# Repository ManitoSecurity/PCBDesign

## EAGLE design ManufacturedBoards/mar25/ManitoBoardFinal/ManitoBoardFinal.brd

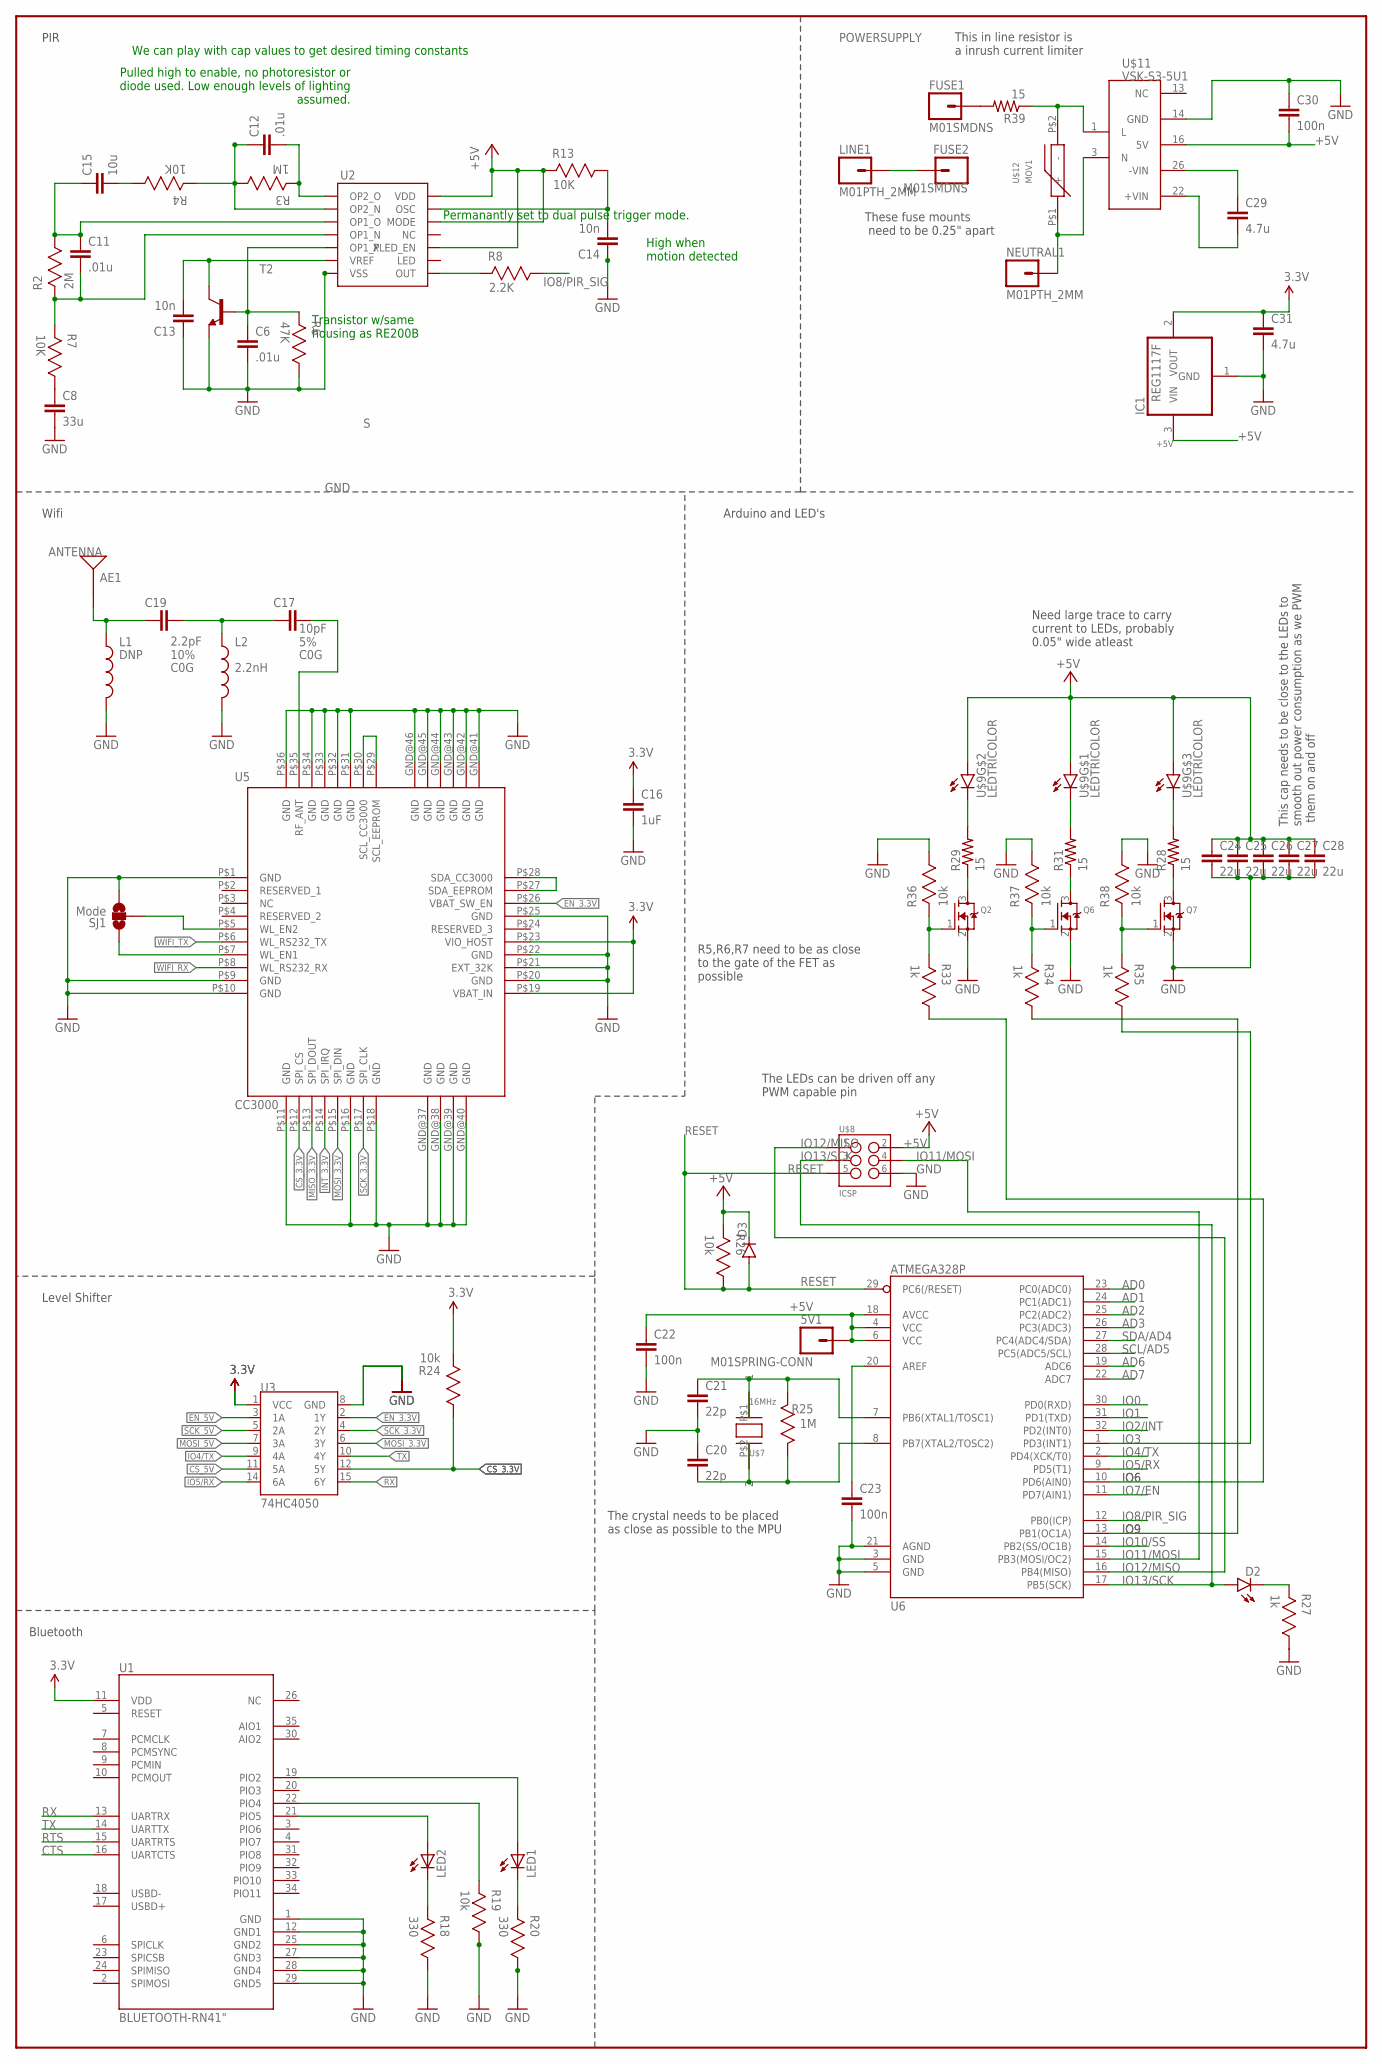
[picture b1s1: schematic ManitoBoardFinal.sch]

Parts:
5V1: M01SPRING-CONN; SPRING-CONNECTOR
AE1: ANTENNA; ANTENNA-CHIP_2500AT44M0400
C6, C11, C12: .01u; 0805
C8: 33u; 0805
C13, C14: 10n; 0805
C15: 10u; 0805
C16: 1uF; 0805
C17: 10pF; 0603-CAP
C19: 2.2pF; 0603-CAP
C20, C21: 22p; 0603-CAP
C22, C23, C30: 100n; 0603-CAP
C24, C25, C26, C27, C28: 22u; 0603-CAP
C29: 4.7u; AXIAL-5MM
C31: 4.7u; 0603-CAP
D2: LED-YELLOW0603; LED-0603
D3: DIODESOD123; SOD-123
FUSE1, FUSE2: M01SMDNS; 1X01NS
IC1: REG1117F; DD-3
L1: DNP; 0603
L2: 2.2nH; 0603
LED1, LED2: LED_ESML0603; LED_SML0603
LINE1: M01PTH_2MM; 1X01_2MM
NEUTRAL1: M01PTH_2MM; 1X01_2MM
Q2, Q6, Q7: MOSFET-NREFLOW; SOT23
R2: 2M; 0603RESISTOR
R3, R25: 1M; 0603RESISTOR
R4, R7, R13: 10K; 0603RESISTOR
R6: 47K; 0603RESISTOR
R8: 2.2K; 0603RESISTOR
R18, R20: 330; 0603RESISTOR
R19, R24, R26, R36, R37, R38: 10k; 0603RESISTOR
R27, R33, R34, R35: 1k; 0603RESISTOR
R28, R29, R31, R39: 15; AXIAL-0.6
SJ1: Mode; SJ_3_PASTE1&2
T2: -NPN-TO5; TO5
U1: BLUETOOTH-RN41"; RN41
U2: NCS36000; SO14
U3: 74HC4050; SO016
U5: CC3000; QFN-46_CC3000
U6: ATMEGA328P; TQFP32-08
U$7: 16MHz; SMDCRYSTAL
U$8: ICSP; 2X3-ICSP
U$9: LEDTRICOLOR; TRICOLORLED
U$11: VSK-S3-5U1; VSK-S3-DCAC
U$12: MOV1; MOV

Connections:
3.3V: C16.1, C31.1, IC1.2 (VOUT), R24.2, U1.11 (VDD), U3.1 (VCC), U5.P$19 (VBAT_IN), U5.P$23 (VIO_HOST)
+5V: 5V1.P$2, C22.1, C24.1, C25.1, C26.1, C27.1, C28.1, C30.2, D3.C, IC1.3 (VIN), R13.2, R26.2, U2.10 (XLED_EN), U2.12 (MODE), U2.14 (VDD), U6.4 (VCC), U6.6 (VCC), U6.18 (AVCC), U$8.2 (+5V), U$9.A1 (A), U$9.A2 (A), U$9.A3 (A), U$11.16 (5V)
AD0: U6.23 (PC0(ADC0))
AD1: U6.24 (PC1(ADC1))
AD2: U6.25 (PC2(ADC2))
AD3: U6.26 (PC3(ADC3))
AD6: U6.19 (ADC6)
AD7: U6.22 (ADC7)
CS_3.3V: R24.1, U3.12 (5Y), U5.P$12 (SPI_CS)
CS_5V: U3.11 (5A)
CTS: U1.16 (UARTCTS)
EN_3.3V: U3.2 (1Y), U5.P$26 (VBAT_SW_EN)
EN_5V: U3.3 (1A)
GND: C6.2, C8.2, C13.1, C14.1, C16.2, C20.1, C21.2, C22.2, C23.2, C24.2, C25.2, C26.2, C27.2, C28.2, C30.1, C31.2, IC1.1 (GND), L1.2, L2.2, Q2.2 (S), Q6.2 (S), Q7.2 (S), R6.1, R18.1, R19.1, R20.1, R27.1, R36.1, R37.1, R38.1, SJ1.3, T2.1 (E), U1.1 (GND), U1.12 (GND1), U1.25 (GND2), U1.27 (GND3), U1.28 (GND4), U1.29 (GND5), U2.7 (VSS), U3.8 (GND), U5.GND@37 (GND), U5.GND@38 (GND), U5.GND@39 (GND), U5.GND@40 (GND), U5.GND@41 (GND), U5.GND@42 (GND), U5.GND@43 (GND), U5.GND@44 (GND), U5.GND@45 (GND), U5.GND@46 (GND), U5.P$1 (GND), U5.P$9 (GND), U5.P$10 (GND), U5.P$11 (GND), U5.P$16 (GND), U5.P$18 (GND), U5.P$20 (GND), U5.P$21 (EXT_32K), U5.P$22 (GND), U5.P$25 (GND), U5.P$31 (GND), U5.P$32 (GND), U5.P$33 (GND), U5.P$34 (GND), U5.P$36 (GND), U6.3 (GND), U6.5 (GND), U6.21 (AGND), U$8.6 (GND), U$11.14 (GND)
INT_3.3V: U5.P$14 (SPI_IRQ)
IO0: U6.30 (PD0(RXD))
IO1: U6.31 (PD1(TXD))
IO2/INT: U6.32 (PD2(INT0))
IO3: R35.1, U6.1 (PD3(INT1))
IO4/TX: U3.9 (4A), U6.2 (PD4(XCK/T0))
IO5/RX: U3.14 (6A), U6.9 (PD5(T1))
IO6: R33.1, U6.10 (PD6(AIN0))
IO7/EN: U6.11 (PD7(AIN1))
IO8/PIR_SIG: R8.1, U6.12 (PB0(ICP))
IO9: R34.1, U6.13 (PB1(OC1A))
IO10/SS: U6.14 (PB2(SS/OC1B))
IO11/MOSI: U6.15 (PB3(MOSI/OC2)), U$8.4 (MOSI)
IO12/MISO: U6.16 (PB4(MISO)), U$8.1 (MISO)
IO13/SCK: D2.A, U6.17 (PB5(SCK)), U$8.3 (SCK)
MISO_3.3V: U5.P$13 (SPI_DOUT)
MOSI_3.3V: U3.6 (3Y), U5.P$15 (SPI_DIN)
MOSI_5V: U3.7 (3A)
unnamed: LED2.C, R18.2
unnamed: C13.2, T2.3 (C), U2.6 (VREF)
unnamed: C11.1, C15.1, R2.1, U2.3 (OP1_O)
unnamed: C11.2, R2.2, R7.2, U2.4 (OP1_N)
unnamed: C12.1, R3.1, R4.2, U2.2 (OP2_N)
unnamed: LED1.C, R20.2
unnamed: C12.2, R3.2, U2.1 (OP2_O)
unnamed: C8.1, R7.1
unnamed: LED2.A, U1.21 (PIO5)
unnamed: R19.2, U1.22 (PIO4)
unnamed: LED1.A, U1.19 (PIO2)
unnamed: C15.2, R4.1
unnamed: C14.2, R13.1, U2.13 (OSC)
unnamed: R8.2, U2.8 (OUT)
unnamed: SJ1.2, U5.P$5 (WL_EN2)
unnamed: SJ1.1, U5.P$7 (WL_EN1)
unnamed: U5.P$27 (SDA_EEPROM), U5.P$28 (SDA_CC3000)
unnamed: U5.P$29 (SCL_EEPROM), U5.P$30 (SCL_CC3000)
unnamed: C17.1, C19.2, L2.1
unnamed: AE1.FEED, C19.1, L1.1
unnamed: C17.2, U5.P$35 (RF_ANT)
unnamed: C20.2, R25.1, U6.8 (PB7(XTAL2/TOSC2)), U$7.P$2 (2)
unnamed: C21.1, R25.2, U6.7 (PB6(XTAL1/TOSC1)), U$7.P$1 (1)
unnamed: C23.1, U6.20 (AREF)
unnamed: D2.C, R27.2
unnamed: R29.P$2 (2), U$9.C2 (C)
unnamed: R31.P$2 (2), U$9.C1 (C)
unnamed: R28.P$2 (2), U$9.C3 (C)
unnamed: Q7.3 (D), R28.P$1 (1)
unnamed: Q6.3 (D), R31.P$1 (1)
unnamed: Q2.3 (D), R29.P$1 (1)
unnamed: Q2.1 (G), R33.2, R36.2
unnamed: Q7.1 (G), R35.2, R38.2
unnamed: Q6.1 (G), R34.2, R37.2
unnamed: C29.P$1 (1), U$11.26 (-VIN)
unnamed: C29.P$2 (2), U$11.22 (+VIN)
unnamed: R39.P$1 (1), U$11.1 (L), U$12.P$2 (-)
unnamed: NEUTRAL1.1, U$11.3 (N), U$12.P$1 (+)
unnamed: FUSE2.1, LINE1.1
unnamed: FUSE1.1, R39.P$2 (2)
RESET: D3.A, R26.1, U6.29 (PC6(/RESET)), U$8.5 (RESET)
RTS: U1.15 (UARTRTS)
RX: U1.13 (UARTRX), U3.15 (6Y)
S: C6.1, R6.2, T2.2 (B), U2.5 (OP1_P)
SCK_3.3V: U3.4 (2Y), U5.P$17 (SPI_CLK)
SCK_5V: U3.5 (2A)
SCL/AD5: U6.28 (PC5(ADC5/SCL))
SDA/AD4: U6.27 (PC4(ADC4/SDA))
TX: U1.14 (UARTTX), U3.10 (4Y)
WIFI_RX: U5.P$8 (WL_RS232_RX)
WIFI_TX: U5.P$6 (WL_RS232_TX)

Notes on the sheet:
Pulled high to enable, no photoresistor or diode used. Low enough levels of lighting assumed.
Permanantly set to dual pulse trigger mode.
High when motion detected
Transistor w/same housing as RE200B
We can play with cap values to get desired timing constants
Level Shifter
PIR
Arduino and LED's
Wifi
Bluetooth
This cap needs to be close to the LEDs to smooth out power consumption as we PWM them on and off
The crystal needs to be placed as close as possible to the MPU
The LEDs can be driven off any PWM capable pin
Need large trace to carry current to LEDs, probably 0.05" wide atleast
R5,R6,R7 need to be as close to the gate of the FET as possible
This in line resistor is a inrush current limiter
These fuse mounts need to be 0.25" apart

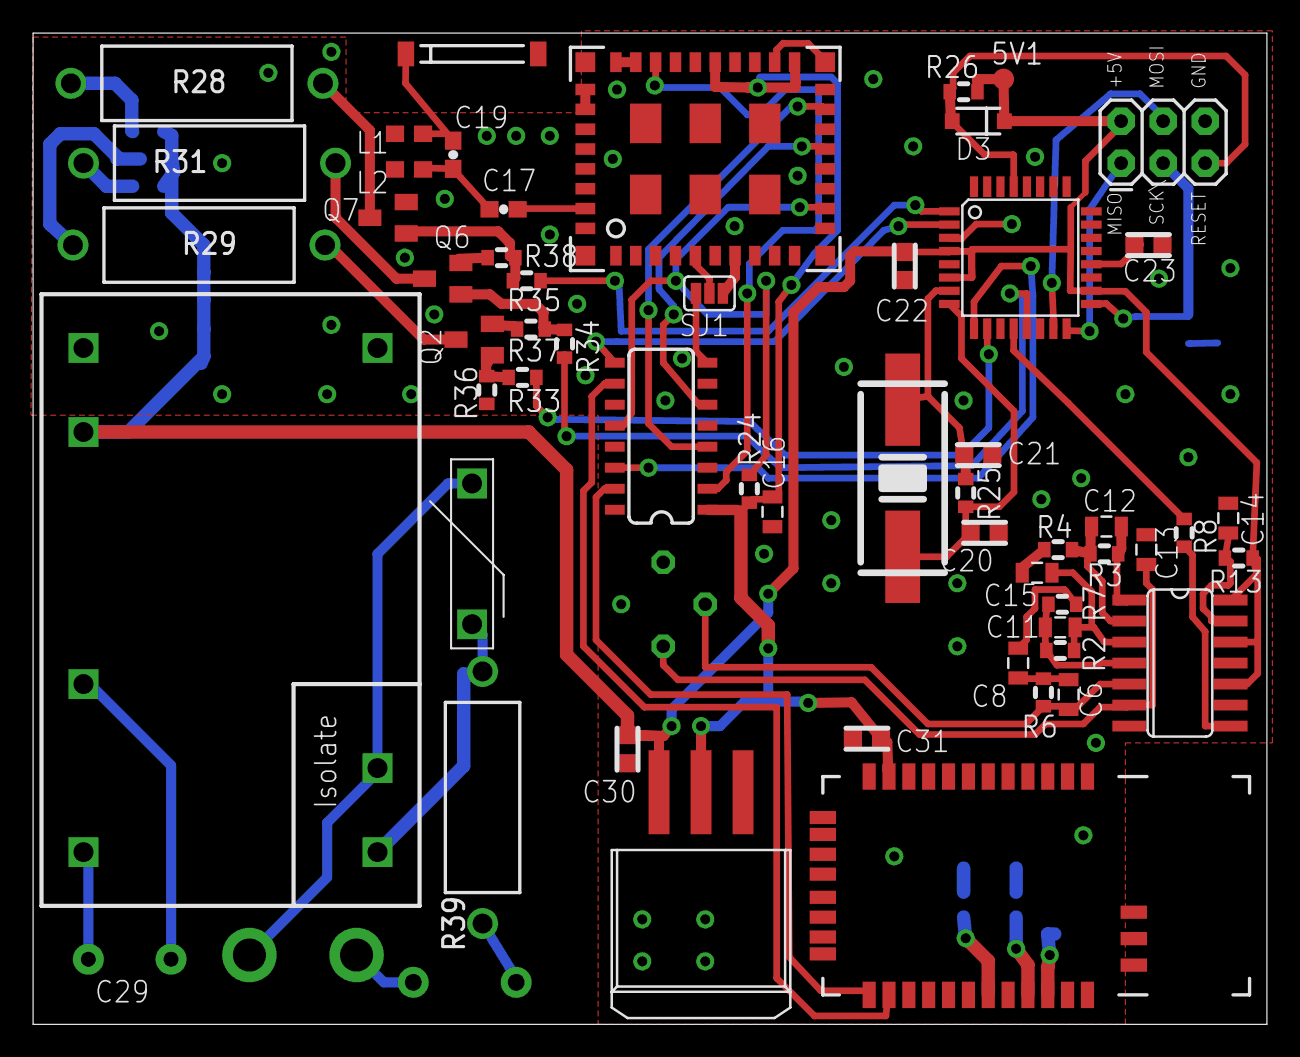
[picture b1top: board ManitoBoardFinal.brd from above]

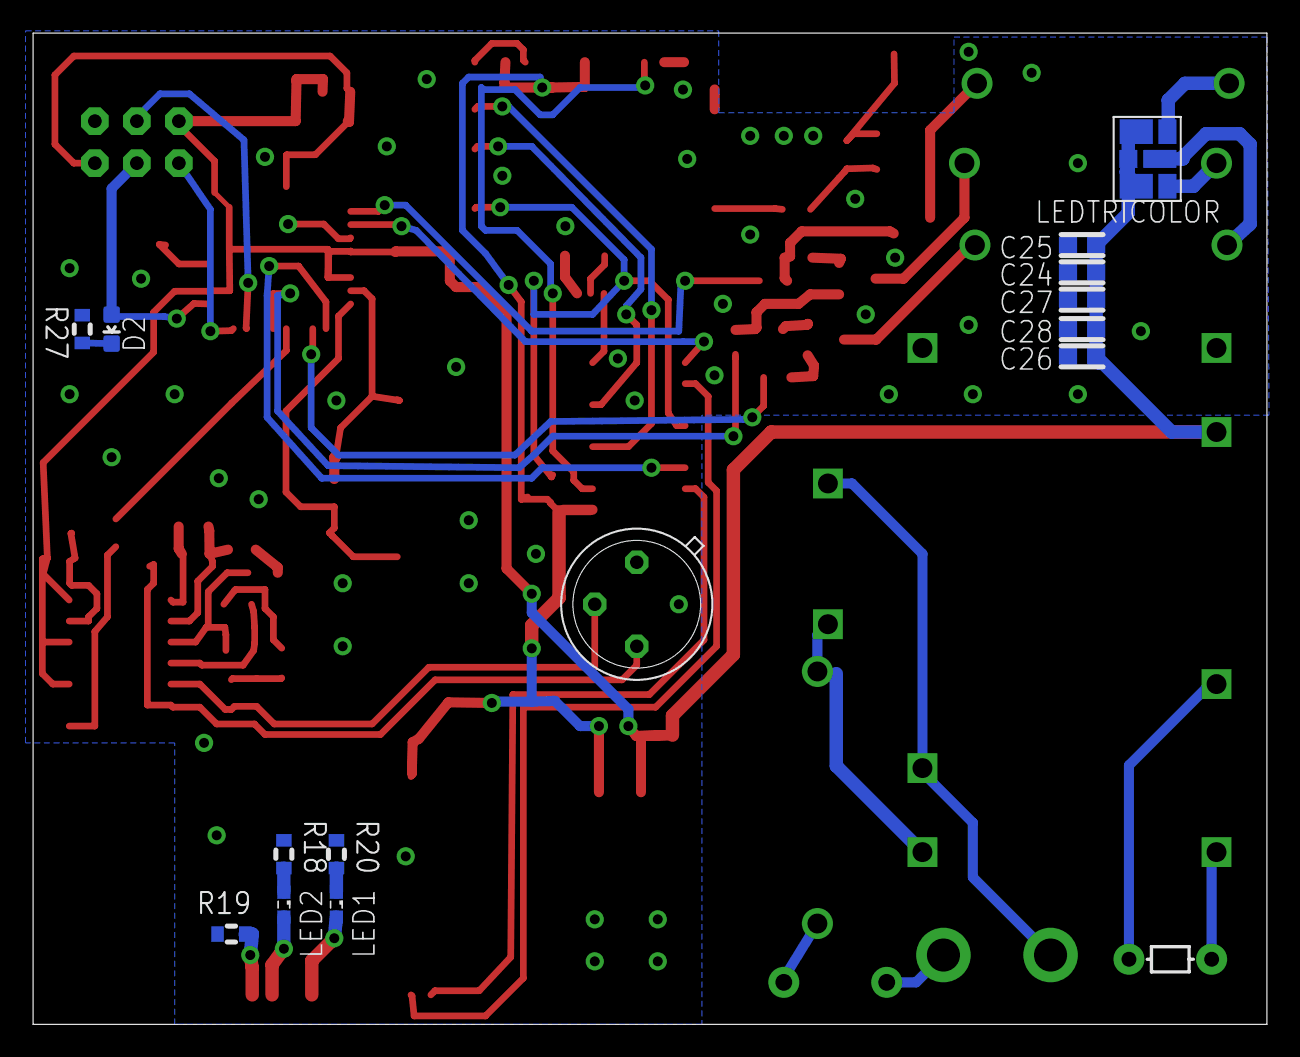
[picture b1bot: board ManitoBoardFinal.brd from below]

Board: 2 copper layers, 74.6 x 59.9 mm, 74 parts (15 on the bottom side), 60 nets.

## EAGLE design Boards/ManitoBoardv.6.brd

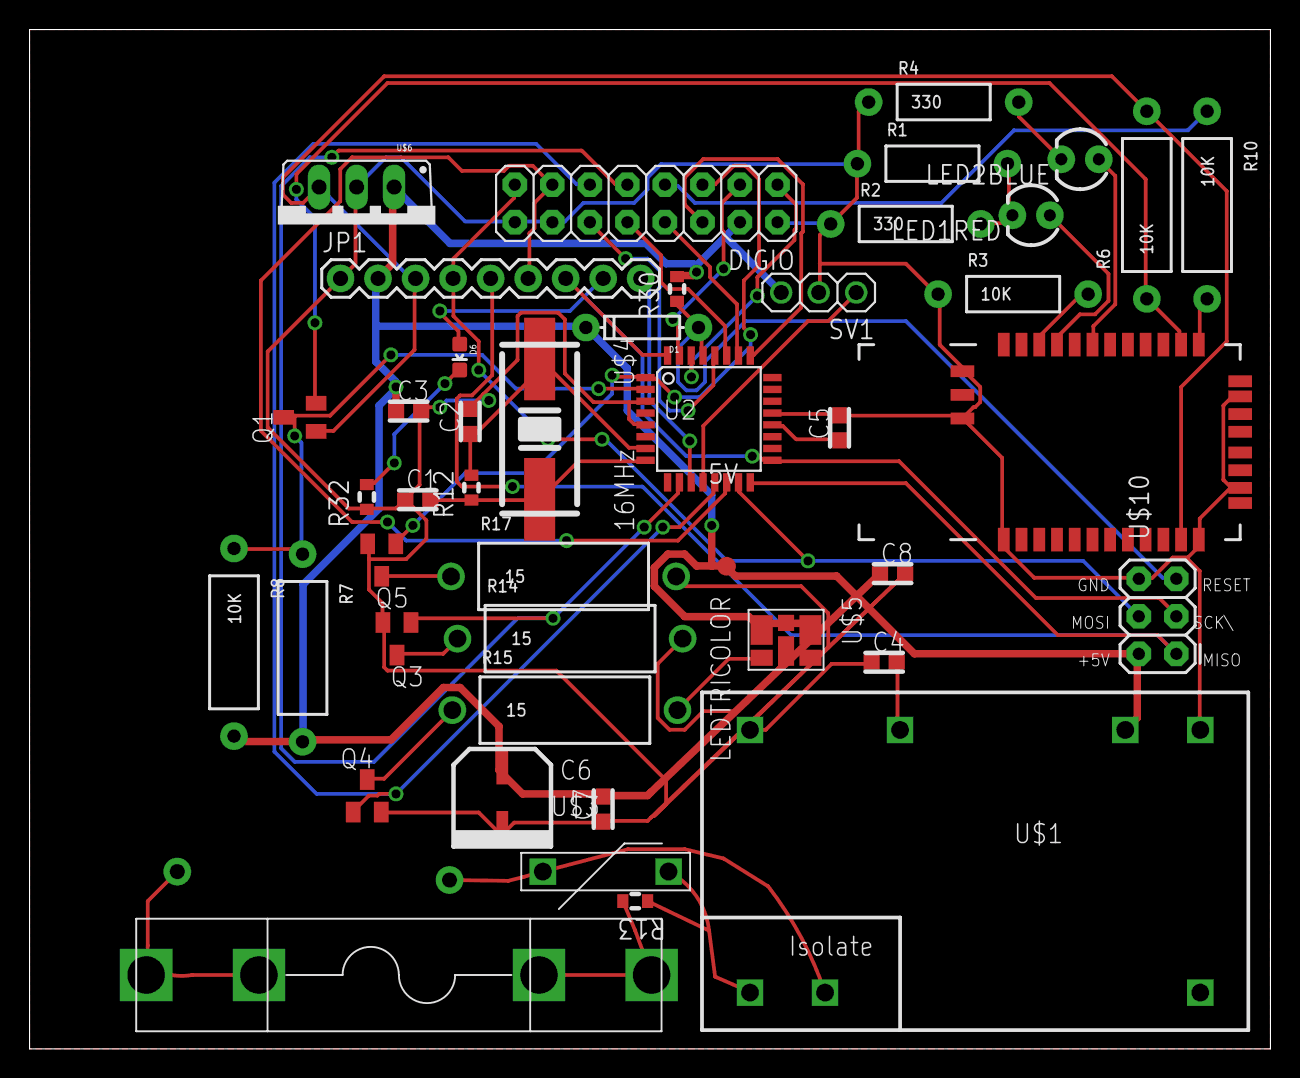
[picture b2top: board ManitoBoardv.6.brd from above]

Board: 2 copper layers, 84.0 x 69.0 mm, 46 parts (0 on the bottom side), 45 nets.

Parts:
5V: M01SPRING-CONN; SPRING-CONNECTOR
C1, C2: 22p; 0603-CAP
C3, C5, C7: 100n; 0603-CAP
C4: 4.7u; 0603-CAP
C6: 100u; WXSERIES-SMDCAP
C8: 100u; 0603-CAP
D1: DIODE-1N4148
D6: LED-0603
DIGIO: M08X2; 2X8
JP1: M09; 1X09
LED1RED, LED2BLUE: LED3MM
LINE: M01SMDNS; 1X01NS
NEUTRAL: M01SMDNS; 1X01NS
Q1, Q3, Q4, Q5: SOT23
R1: AXIAL-0.4
R2, R4: 330; AXIAL-0.4
R3: 10K; AXIAL-0.4
R6, R8, R10: 10K; AXIAL-0.5
R7: AXIAL-0.5
R12: 1M; 0603RESISTOR
R13: 10; 0603RESISTOR
R14, R15, R17: 15; AXIAL-0.6
R30: 10k; 0603RESISTOR
R32: 1k; 0603RESISTOR
SV1: 1X03
U1: BLUETOOTH-RN41"; RN41
U2: ATMEGA328P; TQFP32-08
U$1: VSK-S3-5U1; VSK-S3-DCAC
U$2: 0313.500MXP1; FUSEHOLDER0.25IN
U$3: MOV1; MOV
U$4: 16MHz; SMDCRYSTAL
U$5: LEDTRICOLOR; TRICOLORLED
U$6: UA78M33CKCSE3; TO220
U$10: 6PIN-ICSP; 2X3-ICSP

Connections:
+5V: 5V.P$2, C3.1, C6.POS, C7.2, C8.1, D1.C, DIGIO.4, JP1.2, R7.P$2, R8.P$2, R30.2, SV1.3, U2.4, U2.6, U2.18, U$1.16, U$5.A1, U$5.A2, U$5.A3, U$6.IN, U$10.2
AD2: DIGIO.6, U2.25
AD3: DIGIO.8, U2.26
GND: C1.1, C2.2, C3.2, C5.2, C6.NEG, C7.1, C8.2, DIGIO.2, DIGIO.14, DIGIO.16, JP1.1, Q3.2, Q4.2, Q5.2, R1.P$1, R2.P$1, R3.P$1, R4.P$1, R32.1, SV1.2, U1.1, U1.12, U1.25, U1.27, U1.28, U1.29, U2.3, U2.5, U2.21, U$1.14, U$6.COM, U$10.6
IO0: DIGIO.1, U2.30
IO1: DIGIO.3, U2.31
IO2/INT: JP1.7, U2.32
IO3: DIGIO.5, Q5.1, U2.1
IO4/TX: Q1.3, R7.P$1, R8.P$1, U2.2
IO5/RX: DIGIO.7, R10.P$1
IO6: DIGIO.9, Q3.1, U2.10
IO7/EN: JP1.9, U2.11
IO8/PIR_SIG: SV1.1, U2.12
IO9: DIGIO.11, Q4.1, U2.13
IO10/SS: DIGIO.13, JP1.6, U2.14
IO11/MOSI: DIGIO.15, JP1.4, U2.15, U$10.4
IO12/MISO: JP1.5, U2.16, U$10.1
IO13/SCK: D6.A, JP1.8, U2.17, U$10.3
unnamed: C1.2, R12.1, U2.8, U$4.P$2
unnamed: LED1RED.K, R1.P$2, R2.P$2
unnamed: C2.1, R12.2, U2.7, U$4.P$1
unnamed: Q5.3, R17.P$1
unnamed: Q4.3, R15.P$1
unnamed: Q3.3, R14.P$1
unnamed: C5.1, U2.20
unnamed: D6.C, R32.2
unnamed: C4.1, U$1.26
unnamed: LED2BLUE.K, R4.P$2
unnamed: C4.2, U$1.22
unnamed: R13.1, U$1.1, U$3.P$2
unnamed: NEUTRAL.1, U$1.3, U$3.P$1
unnamed: LINE.1, U$2.P$1, U$2.P$2
unnamed: R13.2, U$2.P$3, U$2.P$4
unnamed: R14.P$2, U$5.C2
unnamed: R15.P$2, U$5.C1
unnamed: R17.P$2, U$5.C3
unnamed: LED1RED.A, U1.21
unnamed: R3.P$2, U1.22
unnamed: LED2BLUE.A, U1.19
RESET: D1.A, R30.1, U2.29, U$10.5
RX: R10.P$2, U1.13
SCL/AD5: DIGIO.12, U2.28
SDA/AD4: DIGIO.10, U2.27
TX: Q1.2, R6.P$1, U1.14
VCC: JP1.3, Q1.1, R6.P$2, U1.11, U$6.OUT

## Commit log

2015-01-17 :neckbeard: Added .gitattributes & .gitignore files
2015-01-17 Board
2015-01-19 Board Development
2015-01-27 Board with Layout
    First complete layout now version .6
2015-02-01 Better Board Layout
2015-02-02 IncompleteRevisions
    Attempting to shrink board size, reduce variety of trace widths,
    simplify angles, remove curved corners, improve thermal relief
2015-02-02 MeetingEdits
2015-02-03 Fixed Layout Issues
2015-02-04 Finished Rev1
2015-02-09 Gerbers
2015-02-15 Assembly
2015-02-25 Updated Schematics for Next Revision
2015-03-06 2nd pcb design iteration
    7.1 design is mostly complete, some changes are still required and must
    undergo DRC. Basic layout should be solid.
2015-03-23 Last Prototype First Attempt
    DRC check must be finished, capacitor under power supply should be
    through hole?, checking hole sizes where needed.
2015-03-23 Second design iteration of final board
    Fixed GND issues and more
2015-03-24 Close to final edits
2015-03-25 Final Board
2015-03-25 SentBoardToManu

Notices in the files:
parts and their libraries:
SparkFun-Connectors: Licensing: Creative Commons ShareAlike 4.0 International - https://creativecommons.org/licenses/by-sa/4.0
SparkFun-RF: Licensing: CC v3.0 Share-Alike You are welcome to use this library for commercial purposes.
